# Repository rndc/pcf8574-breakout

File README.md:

# pcf8574-breakout
PCF8574 Breakout Board

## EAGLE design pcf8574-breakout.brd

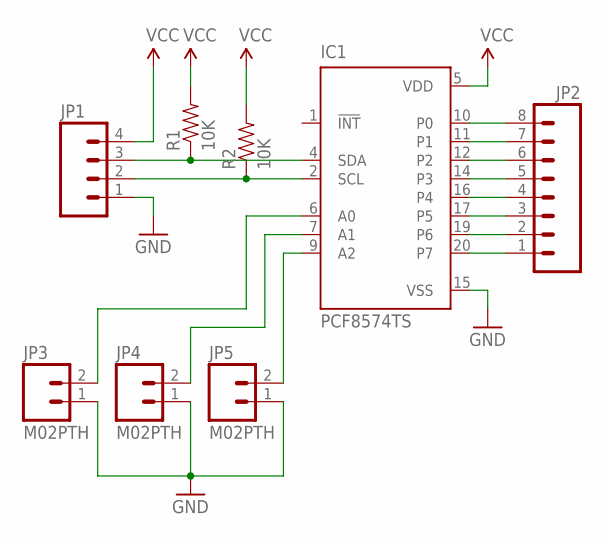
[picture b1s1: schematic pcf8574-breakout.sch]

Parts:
IC1: PCF8574TS; SSOP20
JP1: M04PTH; 1X04
JP2: M081X08; 1X08
JP3, JP4, JP5: M02PTH; 1X02
R1, R2: 10K; 0603-RES

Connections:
GND: IC1.15 (VSS), JP1.1, JP3.1, JP4.1, JP5.1
unnamed: IC1.2 (SCL), JP1.2, R2.1
unnamed: IC1.4 (SDA), JP1.3, R1.1
unnamed: IC1.20 (P7), JP2.1
unnamed: IC1.19 (P6), JP2.2
unnamed: IC1.17 (P5), JP2.3
unnamed: IC1.16 (P4), JP2.4
unnamed: IC1.14 (P3), JP2.5
unnamed: IC1.12 (P2), JP2.6
unnamed: IC1.11 (P1), JP2.7
unnamed: IC1.10 (P0), JP2.8
unnamed: IC1.9 (A2), JP5.2
unnamed: IC1.7 (A1), JP4.2
unnamed: IC1.6 (A0), JP3.2
VCC: IC1.5 (VDD), JP1.4, R1.2, R2.2

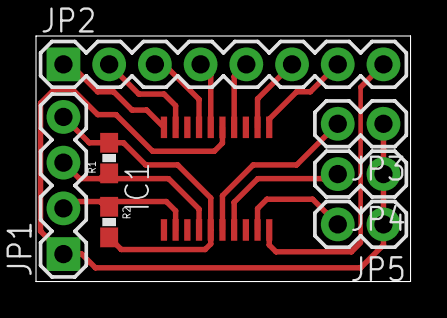
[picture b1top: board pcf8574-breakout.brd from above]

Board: 2 copper layers, 20.8 x 13.6 mm, 8 parts (0 on the bottom side), 15 nets.

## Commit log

2015-02-16 :sparkles: Initial commit

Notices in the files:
parts and their libraries:
SparkFun-Connectors: Licensing: Creative Commons ShareAlike 4.0 International - https://creativecommons.org/licenses/by-sa/4.0
